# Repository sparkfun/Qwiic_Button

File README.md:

SparkFun Qwiic Button
========================================
<table class="table table-hover table-striped table-bordered">
  <tr align="center">
   <td></td>
   <td></td>
   <td></td>
  </tr>
  <tr align="center">
    <td><a href="https://www.sparkfun.com/products/15932">SparkFun Qwiic Button - Red <br />(BOB-15932)</a></td>
    <td><a href="https://www.sparkfun.com/products/16842">SparkFun Qwiic Button - Green <br />(BOB-16842)</a></td>
    <td><a href="https://www.sparkfun.com/products/15931">SparkFun Qwiic Button Breakout <br />(BOB-15931)</a></td>
  </tr>
</table>

The SparkFun Qwiic Button is an I<sup>2</sup>C enabled button with a built-in LED, interrupts, variable I<sup>2</sup>C address, and onboard button queues.

Repository Contents
-------------------

* **/Documentation** - Data sheets, additional product information
* **/Hardware** - Eagle design files (.brd, .sch)
* **/Firmware** - The latest firmware on the Qwiic Button boards
* **/Hardware/Production** - Production panel files (.brd)

Documentation
--------------
* **[SparkFun Qwiic Button Hookup Guide](https://learn.sparkfun.com/tutorials/sparkfun-qwiic-button-hookup-guide/all)** - Basic Hookup Guide.
* **[SparkFun Qwiic Button Arduino Library](https://github.com/sparkfun/SparkFun_Qwiic_Button_Arduino_Library)** - Arduino library for the Qwiic Button and Switch.
* **[SparkFun Qwiic Button Python Package](https://github.com/sparkfun/Qwiic_Button_Py)** - Python package for the Qwiic Button and Qwiic Switch

Product Versions
--------------

* [BOB-15932](https://www.sparkfun.com/products/15932) - SparkFun Red Version with red LED pushbutton
* [BOB-16842](https://www.sparkfun.com/products/16842) - SparkFun Red Version with green LED pushbutton
* [BOB-15931](https://www.sparkfun.com/products/15931) - SparkFun Red Version without button
* [SPX-15584](https://www.sparkfun.com/products/15584) - Original SparkX version of the Qwiic Button.

License Information
-------------------

This product is _**open source**_! 

Please review the LICENSE.md file for license information. 

If you have any questions or concerns on licensing, please contact technical support on our [SparkFun forums](https://forum.sparkfun.com/viewforum.php?f=152).

Distributed as-is; no warranty is given.

- Your friends at SparkFun.

_<COLLABORATION CREDIT>_

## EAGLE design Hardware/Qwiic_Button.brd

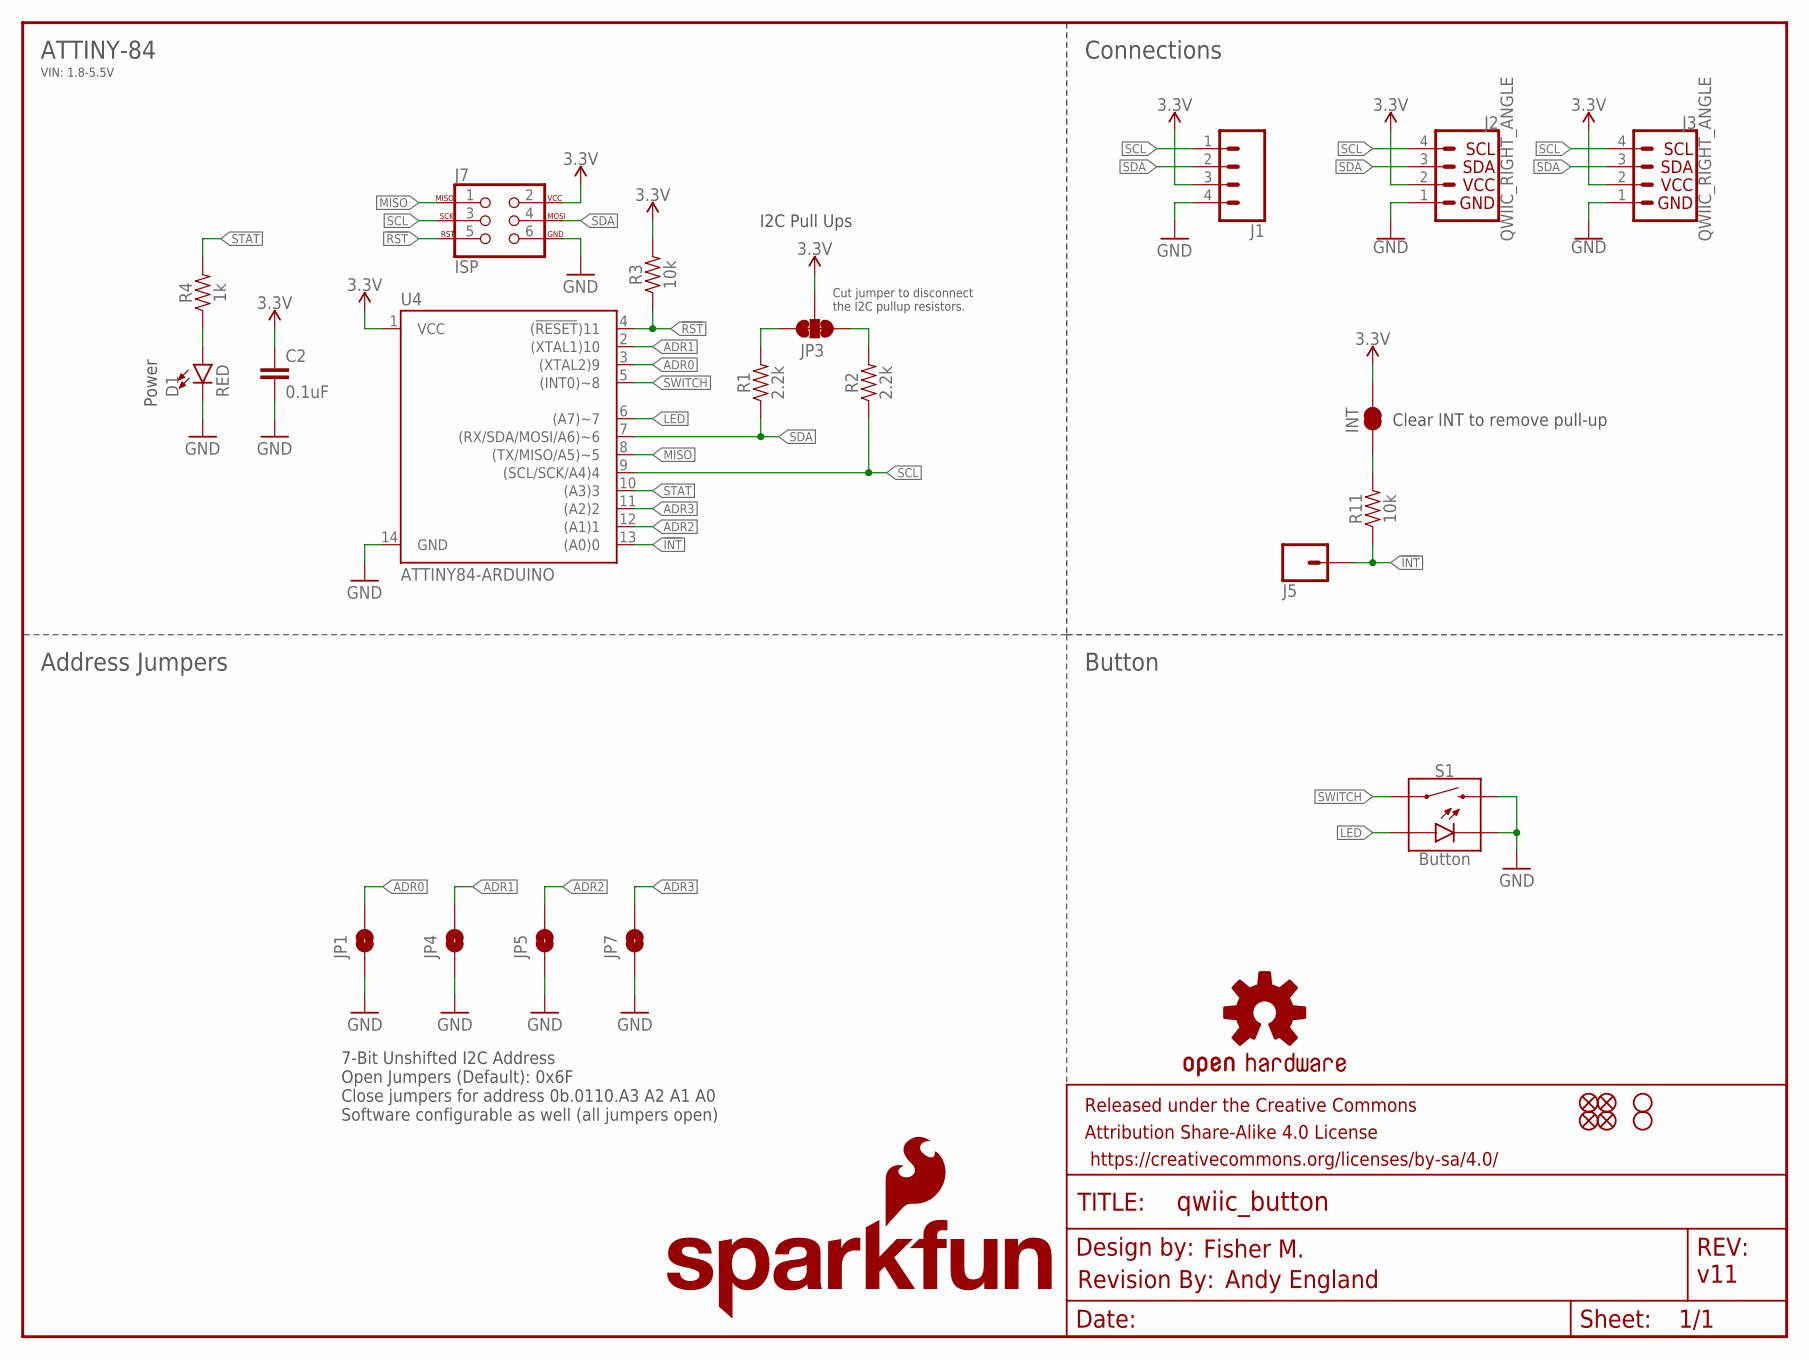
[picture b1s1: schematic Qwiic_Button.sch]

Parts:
C2: 0.1uF; 0603
D1: RED; LED-0603
FRAME1: FRAME-LETTER; CREATIVE_COMMONS
H1, H2: STAND-OFF
INT: JUMPER-SMT_2_NC_TRACE_SILK; SMT-JUMPER_2_NC_TRACE_SILK
J1: CONN_041X04_NO_SILK; 1X04_NO_SILK
J2, J3: QWIIC_RIGHT_ANGLE; JST04_1MM_RA
J5: CONN_01PTH_NO_SILK_YES_STOP; 1X01_NO_SILK
J7: ISP; 2X3_TEST_POINTS
JP1, JP4, JP5, JP7: JUMPER-SMT_2_NO_NO-SILK; SMT-JUMPER_2_NO_NO-SILK
JP2, JP6, JP8, JP9: FIDUCIALUFIDUCIAL; MICRO-FIDUCIAL
JP3: JUMPER-SMT_3_2-NC_TRACE_SILK; SMT-JUMPER_3_2-NC_TRACE_SILK
LOGO1: OSHW-LOGOMINI; OSHW-LOGO-MINI
LOGO2: REVISION
LOGO3: SFE_LOGO_NAME.1_INCH; SFE_LOGO_NAME_.1
LOGO4: SFE_LOGO_FLAME.1_INCH; SFE_LOGO_FLAME_.1
R1, R2: 2.2k; 0603
R3, R11: 10k; 0603
R4: 1k; 0603
S1: Button; TACTILE_SWITCH_LED_PTH_12MM
U4: ATTINY84-ARDUINO; SO14

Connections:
3.3V: C2.1, INT.2, J1.3, J2.2, J3.2, J7.2, JP3.2, R3.2, U4.1 (VCC)
!INT: J5.1, R11.1, U4.13 ((A0)0)
!RST: J7.5, R3.1, U4.4 ((!RESET!)11)
ADR0: JP1.2, U4.3 ((XTAL2)9)
ADR1: JP4.2, U4.2 ((XTAL1)10)
ADR2: JP5.2, U4.12 ((A1)1)
ADR3: JP7.2, U4.11 ((A2)2)
GND: C2.2, D1.C, J1.4, J2.1, J3.1, J7.6, JP1.1, JP4.1, JP5.1, JP7.1, S1.2, S1.C, U4.14 (GND)
INT_R: INT.1, R11.2
LED: S1.A, U4.6 ((A7)~7)
MISO: J7.1, U4.8 ((TX/MISO/A5)~5)
unnamed: D1.A, R4.1
SCL: J1.1, J2.4, J3.4, J7.3, R2.1, U4.9 ((SCL/SCK/A4)4)
SCL_PU1: JP3.1, R2.2
SDA: J1.2, J2.3, J3.3, J7.4, R1.1, U4.7 ((RX/SDA/MOSI/A6)~6)
SDA_PU1: JP3.3, R1.2
STAT: R4.2, U4.10 ((A3)3)
SWITCH: S1.4 (1), U4.5 ((INT0)~8)

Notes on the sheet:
v11
Connections
Cut jumper to disconnect the I2C pullup resistors.
7-Bit Unshifted I2C Address Open Jumpers (Default): 0x6F Close jumpers for address 0b.0110.A3 A2 A1 A0 Software configurable as well (all jumpers open)
I2C Pull Ups
Power
Clear INT to remove pull-up
Fisher M.
Andy England
ATTINY-84
Address Jumpers
Button
VIN: 1.8-5.5V

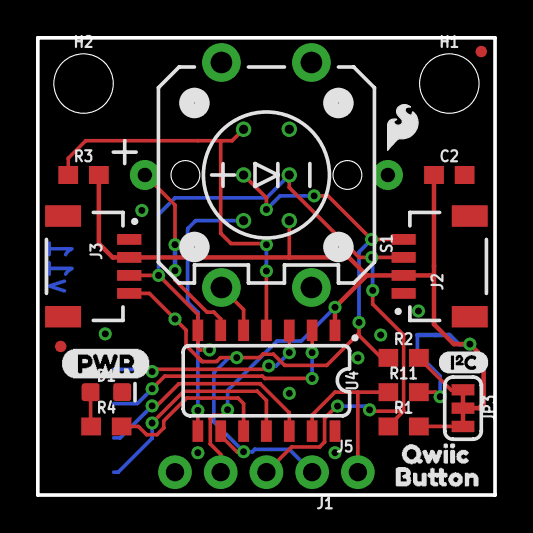
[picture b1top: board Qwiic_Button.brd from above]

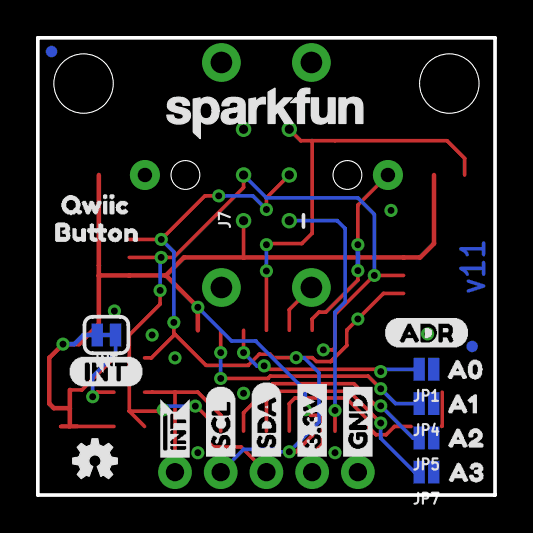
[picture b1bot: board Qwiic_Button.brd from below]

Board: 2 copper layers, 25.4 x 25.4 mm, 48 parts (23 on the bottom side), 18 nets.

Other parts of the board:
U$1, U$2: BUTTON1
U$3: PWR-()-04
U$4: INT-()-04
U$5: SCL
U$6: SDA
U$7: 3.3V
U$8: GND
U$9: (ADR)
U$10: I_SUPER2_C-()-03
U$15: INT#-[<-04
U$16: A00
U$17: A11
U$19: A22
U$20, U$23: QWIIC0
U$21: A33

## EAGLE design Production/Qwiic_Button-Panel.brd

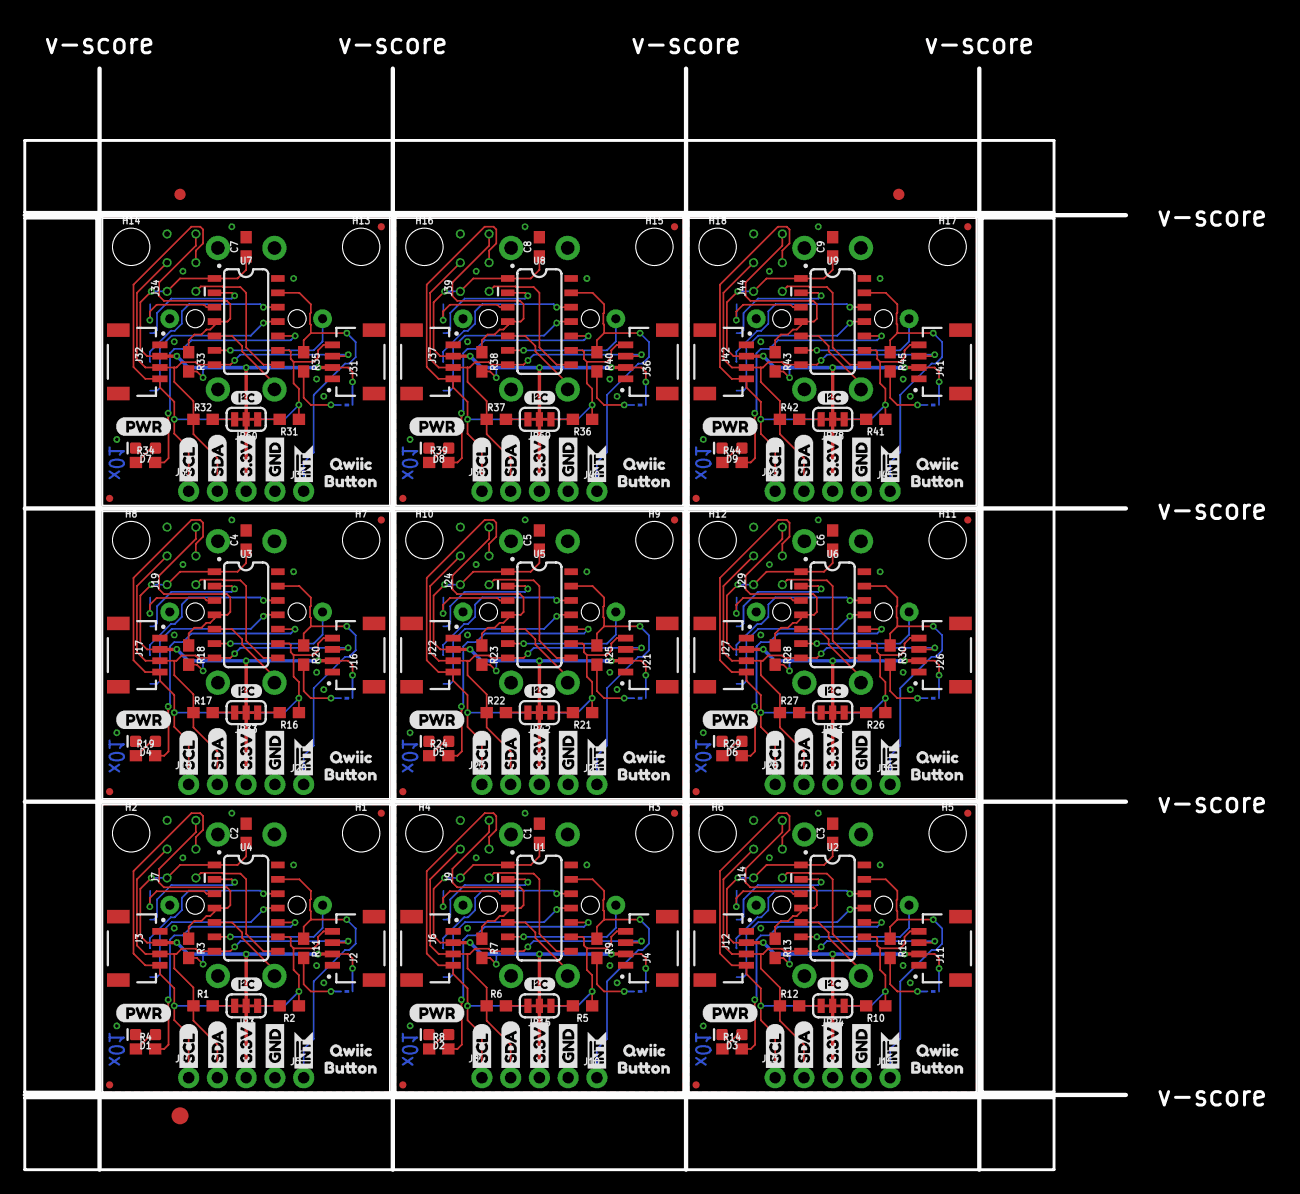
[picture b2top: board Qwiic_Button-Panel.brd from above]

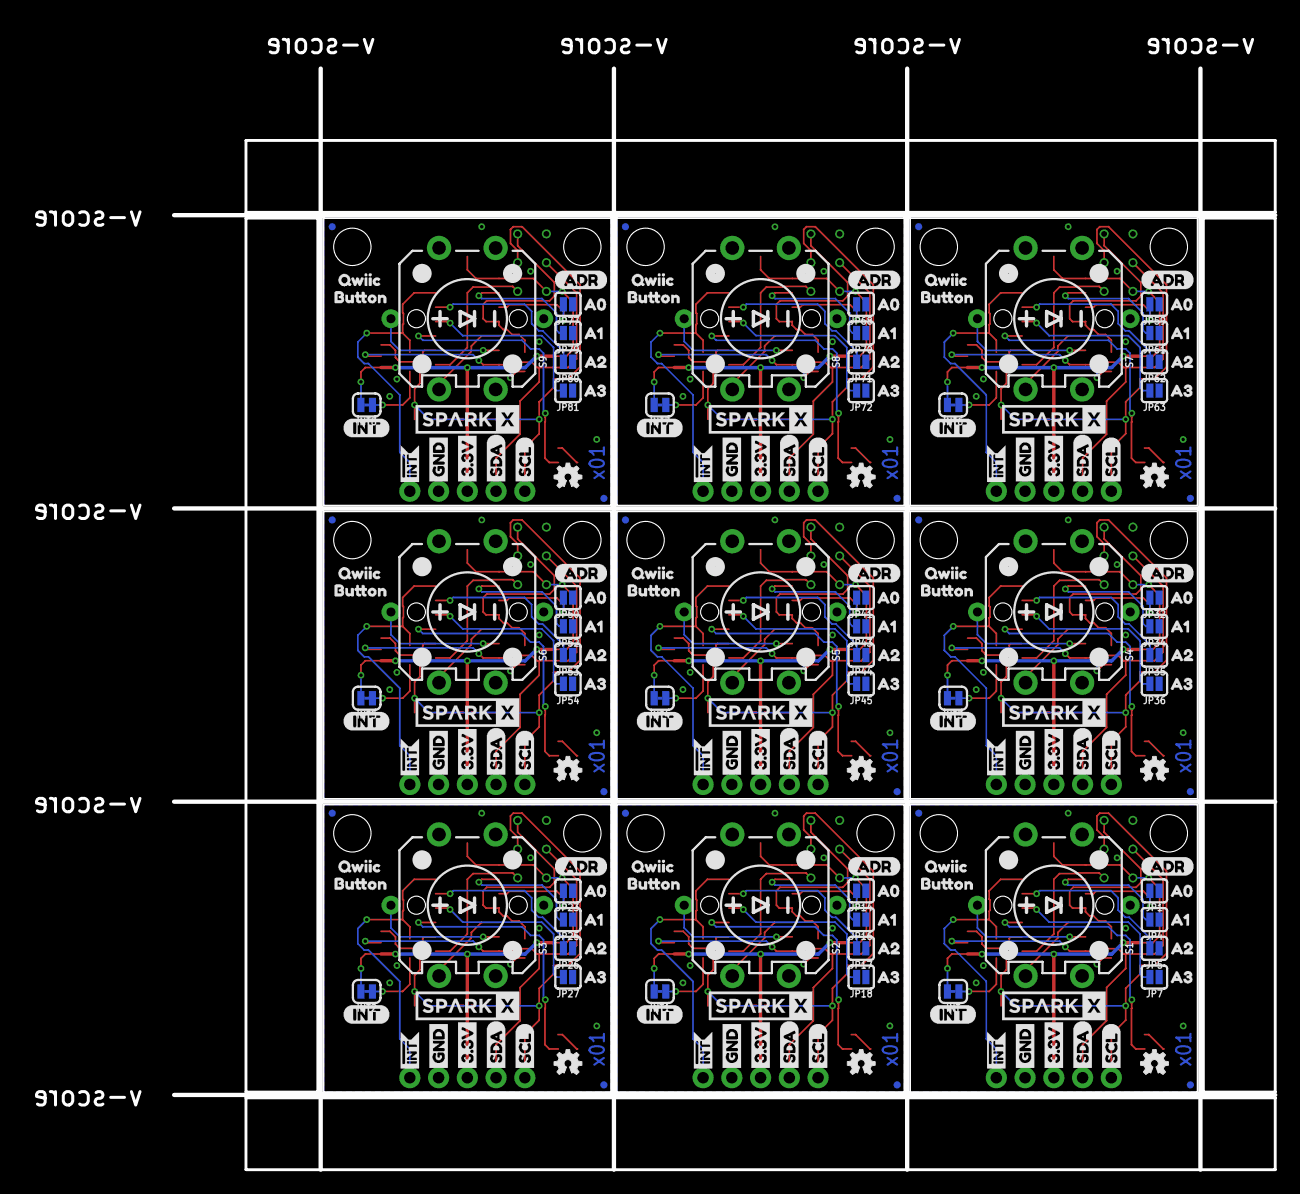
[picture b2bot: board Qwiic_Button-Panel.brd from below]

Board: 2 copper layers, 97.3 x 97.3 mm, 453 parts (207 on the bottom side), 162 nets.

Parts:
C1, C2, C3, C4, C5, C6, C7, C8, C9: 0.1uF; 0603
D1, D2, D3, D4, D5, D6, D7, D8, D9: RED; LED-0603
E$1, E$2: FIDUCIAL-1X2
E$3: FIDUCIAL-1.5X3
H1, H2, H3, H4, H5, H6, H7, H8, H9, H10, H11, H12, H13, H14, H15, H16, H17, H18: STAND-OFF
INT, INT1, INT2, INT3, INT4, INT5, INT6, INT7, INT8: SMT-JUMPER_2_NC_TRACE_SILK
J1, J8, J13, J18, J23, J28, J33, J38, J43: 1X04_NO_SILK
J2, J3, J4, J6, J11, J12, J16, J17, J21, J22, J26, J27, J31, J32, J36, J37, J41, J42: JST04_1MM_RA
J5, J10, J15, J20, J25, J30, J35, J40, J45: 1X01_NO_SILK
J7, J9, J14, J19, J24, J29, J34, J39, J44: ISP; 2X3_TEST_POINTS
JP1, JP4, JP5, JP7, JP14, JP16, JP17, JP18, JP23, JP25, JP26, JP27, JP32, JP34, JP35, JP36, JP41, JP43, JP44, JP45, JP50, JP52, JP53, JP54, JP59, JP61, JP62, JP63, JP68, JP70, JP71, JP72, JP77, JP79, JP80, JP81: SMT-JUMPER_2_NO_SILK
JP2, JP6, JP8, JP9, JP10, JP11, JP12, JP13, JP19, JP20, JP21, JP22, JP28, JP29, JP30, JP31, JP37, JP38, JP39, JP40, JP46, JP47, JP48, JP49, JP55, JP56, JP57, JP58, JP64, JP65, JP66, JP67, JP73, JP74, JP75, JP76: FIDUCIALUFIDUCIAL; MICRO-FIDUCIAL
JP3, JP15, JP24, JP33, JP42, JP51, JP60, JP69, JP78: SMT-JUMPER_3_2-NC_TRACE_SILK
LOGO1, LOGO2, LOGO3, LOGO4, LOGO5, LOGO6, LOGO7, LOGO8, LOGO9: OSHW-LOGOMINI; OSHW-LOGO-MINI
R1, R2, R5, R6, R10, R12, R16, R17, R21, R22, R26, R27, R31, R32, R36, R37, R41, R42: 2.2k; 0603
R3, R7, R9, R11, R13, R15, R18, R20, R23, R25, R28, R30, R33, R35, R38, R40, R43, R45: 10k; 0603
R4, R8, R14, R19, R24, R29, R34, R39, R44: 1k; 0603
S1, S2, S3, S4, S5, S6, S7, S8, S9: Button; TACTILE_SWITCH_LED_PTH_12MM
U1, U2, U3, U4, U5, U6, U7, U8, U9: ATTINY84-ARDUINO; SO14
U$1, U$2, U$38, U$39, U$61, U$62, U$84, U$85, U$107, U$108, U$130, U$131, U$153, U$154, U$176, U$177, U$199, U$200: BUTTON1
U$3, U$42, U$65, U$88, U$111, U$134, U$157, U$180, U$203: PWR-()-04
U$4, U$37, U$60, U$83, U$106, U$129, U$152, U$175, U$198: INT-()-04
U$5, U$14, U$24, U$34, U$47, U$57, U$70, U$80, U$93, U$103, U$116, U$126, U$139, U$149, U$162, U$172, U$185, U$195: SCL
U$6, U$12, U$25, U$33, U$48, U$56, U$71, U$79, U$94, U$102, U$117, U$125, U$140, U$148, U$163, U$171, U$186, U$194: SDA
U$7, U$22, U$26, U$30, U$49, U$53, U$72, U$76, U$95, U$99, U$118, U$122, U$141, U$145, U$164, U$168, U$187, U$191: 3.3V
U$8, U$13, U$27, U$29, U$50, U$52, U$73, U$75, U$96, U$98, U$119, U$121, U$142, U$144, U$165, U$167, U$188, U$190: GND
U$9, U$28, U$51, U$74, U$97, U$120, U$143, U$166, U$189: (ADR)
U$10, U$31, U$54, U$77, U$100, U$123, U$146, U$169, U$192: I_SUPER2_C-()-03
U$11, U$15, U$32, U$35, U$55, U$58, U$78, U$81, U$101, U$104, U$124, U$127, U$147, U$150, U$170, U$173, U$193, U$196: INT#-[<-04
U$16, U$43, U$66, U$89, U$112, U$135, U$158, U$181, U$204: A00
U$17, U$44, U$67, U$90, U$113, U$136, U$159, U$182, U$205: A11
U$18, U$36, U$59, U$82, U$105, U$128, U$151, U$174, U$197: SPARKX-MEDIUM
U$19, U$45, U$68, U$91, U$114, U$137, U$160, U$183, U$206: A22
U$20, U$23, U$40, U$41, U$63, U$64, U$86, U$87, U$109, U$110, U$132, U$133, U$155, U$156, U$178, U$179, U$201, U$202: QWIIC0
U$21, U$46, U$69, U$92, U$115, U$138, U$161, U$184, U$207: A33

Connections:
3.3V: C2.1, INT.2, J1.3, J2.2, J3.2, J7.2, JP3.2, R3.2, U4.1
3.3V1: C1.1, INT1.2, J4.2, J6.2, J8.3, J9.2, JP15.2, R7.2, U1.1
3.3V2: C3.1, INT2.2, J11.2, J12.2, J13.3, J14.2, JP24.2, R13.2, U2.1
3.3V3: C4.1, INT3.2, J16.2, J17.2, J18.3, J19.2, JP33.2, R18.2, U3.1
3.3V4: C5.1, INT4.2, J21.2, J22.2, J23.3, J24.2, JP42.2, R23.2, U5.1
3.3V5: C6.1, INT5.2, J26.2, J27.2, J28.3, J29.2, JP51.2, R28.2, U6.1
3.3V6: C7.1, INT6.2, J31.2, J32.2, J33.3, J34.2, JP60.2, R33.2, U7.1
3.3V7: C8.1, INT7.2, J36.2, J37.2, J38.3, J39.2, JP69.2, R38.2, U8.1
3.3V8: C9.1, INT8.2, J41.2, J42.2, J43.3, J44.2, JP78.2, R43.2, U9.1
!INT: J5.1, R11.1, U4.13
!INT1: J10.1, R9.1, U1.13
!INT2: J15.1, R15.1, U2.13
!INT3: J20.1, R20.1, U3.13
!INT4: J25.1, R25.1, U5.13
!INT5: J30.1, R30.1, U6.13
!INT6: J35.1, R35.1, U7.13
!INT7: J40.1, R40.1, U8.13
!INT8: J45.1, R45.1, U9.13
!RST: J7.5, R3.1, U4.4
!RST1: J9.5, R7.1, U1.4
!RST2: J14.5, R13.1, U2.4
!RST3: J19.5, R18.1, U3.4
!RST4: J24.5, R23.1, U5.4
!RST5: J29.5, R28.1, U6.4
!RST6: J34.5, R33.1, U7.4
!RST7: J39.5, R38.1, U8.4
!RST8: J44.5, R43.1, U9.4
ADR0: JP1.2, U4.3
ADR1: JP4.2, U4.2
ADR2: JP5.2, U4.12
ADR3: JP7.2, U4.11
ADR4: JP14.2, U1.3
ADR5: JP16.2, U1.2
ADR6: JP17.2, U1.12
ADR7: JP18.2, U1.11
ADR8: JP23.2, U2.3
ADR9: JP25.2, U2.2
ADR10: JP26.2, U2.12
ADR11: JP27.2, U2.11
ADR12: JP32.2, U3.3
ADR13: JP34.2, U3.2
ADR14: JP35.2, U3.12
ADR15: JP36.2, U3.11
ADR16: JP41.2, U5.3
ADR17: JP43.2, U5.2
ADR18: JP44.2, U5.12
ADR19: JP45.2, U5.11
ADR20: JP50.2, U6.3
ADR21: JP52.2, U6.2
ADR22: JP53.2, U6.12
ADR23: JP54.2, U6.11
ADR24: JP59.2, U7.3
ADR25: JP61.2, U7.2
ADR26: JP62.2, U7.12
ADR27: JP63.2, U7.11
ADR28: JP68.2, U8.3
ADR29: JP70.2, U8.2
ADR30: JP71.2, U8.12
ADR31: JP72.2, U8.11
ADR32: JP77.2, U9.3
ADR33: JP79.2, U9.2
ADR34: JP80.2, U9.12
ADR35: JP81.2, U9.11
GND: C2.2, D1.C, J1.4, J2.1, J3.1, J7.6, JP1.1, JP4.1, JP5.1, JP7.1, S1.2, S1.C, U4.14
GND1: C1.2, D2.C, J4.1, J6.1, J8.4, J9.6, JP14.1, JP16.1, JP17.1, JP18.1, S2.2, S2.C, U1.14
GND2: C3.2, D3.C, J11.1, J12.1, J13.4, J14.6, JP23.1, JP25.1, JP26.1, JP27.1, S3.2, S3.C, U2.14
GND3: C4.2, D4.C, J16.1, J17.1, J18.4, J19.6, JP32.1, JP34.1, JP35.1, JP36.1, S4.2, S4.C, U3.14
GND4: C5.2, D5.C, J21.1, J22.1, J23.4, J24.6, JP41.1, JP43.1, JP44.1, JP45.1, S5.2, S5.C, U5.14
GND5: C6.2, D6.C, J26.1, J27.1, J28.4, J29.6, JP50.1, JP52.1, JP53.1, JP54.1, S6.2, S6.C, U6.14
GND6: C7.2, D7.C, J31.1, J32.1, J33.4, J34.6, JP59.1, JP61.1, JP62.1, JP63.1, S7.2, S7.C, U7.14
GND7: C8.2, D8.C, J36.1, J37.1, J38.4, J39.6, JP68.1, JP70.1, JP71.1, JP72.1, S8.2, S8.C, U8.14
GND8: C9.2, D9.C, J41.1, J42.1, J43.4, J44.6, JP77.1, JP79.1, JP80.1, JP81.1, S9.2, S9.C, U9.14
INT_R: INT.1, R11.2
INT_R1: INT1.1, R9.2
INT_R2: INT2.1, R15.2
INT_R3: INT3.1, R20.2
INT_R4: INT4.1, R25.2
INT_R5: INT5.1, R30.2
INT_R6: INT6.1, R35.2
INT_R7: INT7.1, R40.2
INT_R8: INT8.1, R45.2
LED: S1.A, U4.6
LED1: S2.A, U1.6
LED2: S3.A, U2.6
LED3: S4.A, U3.6
LED4: S5.A, U5.6
LED5: S6.A, U6.6
LED6: S7.A, U7.6
LED7: S8.A, U8.6
LED8: S9.A, U9.6
MISO: J7.1, U4.8
MISO1: J9.1, U1.8
MISO2: J14.1, U2.8
MISO3: J19.1, U3.8
MISO4: J24.1, U5.8
MISO5: J29.1, U6.8
MISO6: J34.1, U7.8
MISO7: J39.1, U8.8
MISO8: J44.1, U9.8
unnamed: D2.A, R8.1
unnamed: D3.A, R14.1
unnamed: D1.A, R4.1
unnamed: D4.A, R19.1
unnamed: D5.A, R24.1
unnamed: D6.A, R29.1
unnamed: D7.A, R34.1
unnamed: D8.A, R39.1
unnamed: D9.A, R44.1
SCL: J1.1, J2.4, J3.4, J7.3, R2.1, U4.9
SCL1: J4.4, J6.4, J8.1, J9.3, R5.1, U1.9
SCL2: J11.4, J12.4, J13.1, J14.3, R10.1, U2.9
SCL3: J16.4, J17.4, J18.1, J19.3, R16.1, U3.9
SCL4: J21.4, J22.4, J23.1, J24.3, R21.1, U5.9
SCL5: J26.4, J27.4, J28.1, J29.3, R26.1, U6.9
SCL6: J31.4, J32.4, J33.1, J34.3, R31.1, U7.9
SCL7: J36.4, J37.4, J38.1, J39.3, R36.1, U8.9
SCL8: J41.4, J42.4, J43.1, J44.3, R41.1, U9.9
SCL_PU1: JP3.1, R2.2
SCL_PU2: JP15.1, R5.2
SCL_PU3: JP24.1, R10.2
SCL_PU4: JP33.1, R16.2
SCL_PU5: JP42.1, R21.2
SCL_PU6: JP51.1, R26.2
SCL_PU7: JP60.1, R31.2
SCL_PU8: JP69.1, R36.2
SCL_PU9: JP78.1, R41.2
SDA: J1.2, J2.3, J3.3, J7.4, R1.1, U4.7
SDA1: J4.3, J6.3, J8.2, J9.4, R6.1, U1.7
SDA2: J11.3, J12.3, J13.2, J14.4, R12.1, U2.7
SDA3: J16.3, J17.3, J18.2, J19.4, R17.1, U3.7
SDA4: J21.3, J22.3, J23.2, J24.4, R22.1, U5.7
SDA5: J26.3, J27.3, J28.2, J29.4, R27.1, U6.7
SDA6: J31.3, J32.3, J33.2, J34.4, R32.1, U7.7
SDA7: J36.3, J37.3, J38.2, J39.4, R37.1, U8.7
SDA8: J41.3, J42.3, J43.2, J44.4, R42.1, U9.7
SDA_PU1: JP3.3, R1.2
SDA_PU2: JP15.3, R6.2
SDA_PU3: JP24.3, R12.2
SDA_PU4: JP33.3, R17.2
SDA_PU5: JP42.3, R22.2
SDA_PU6: JP51.3, R27.2
SDA_PU7: JP60.3, R32.2
SDA_PU8: JP69.3, R37.2
SDA_PU9: JP78.3, R42.2
STAT: R4.2, U4.10
STAT1: R8.2, U1.10
STAT2: R14.2, U2.10
STAT3: R19.2, U3.10
STAT4: R24.2, U5.10
STAT5: R29.2, U6.10
STAT6: R34.2, U7.10
STAT7: R39.2, U8.10
STAT8: R44.2, U9.10
SWITCH: S1.4, U4.5
SWITCH1: S2.4, U1.5
SWITCH2: S3.4, U2.5
SWITCH3: S4.4, U3.5
SWITCH4: S5.4, U5.5
SWITCH5: S6.4, U6.5
SWITCH6: S7.4, U7.5
SWITCH7: S8.4, U8.5
SWITCH8: S9.4, U9.5

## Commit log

2019-11-27 changing silk, moving everything to one side for production
2019-12-02 post design review changes
2019-12-03 post checklist changes
2020-01-23 Create gitignore file.
    Added file.
2020-01-23 Create License.md file
    Added file.
2020-01-23 Create Issue Template File
    Added file.
2020-01-23 Created contributing file
    Added file.
2020-01-23 Updated ReadMe to add Hookup Guide
    Added Hookup Guide link.
2020-01-23 Update ReadMe
    Added links to SparkFun versions of Qwiic Button and Qwiic Button Breakout along with Hookup Guide. Updated photos for SparkFun version of Qwiic Buttons.
2020-01-23 cleaning repo for release, removing backup files
2020-01-23 adding polarity marker to button
2020-01-23 Update ReadMe
    Added Firmware to Repository Contents list.
2020-01-23 Update ReadMe
    Adding SparkX Product version for Qwiic Button (Red)
2020-01-23 Update ReadMe
    Removing old Firmware link from ReadMe. Firmware is now in the Repository Contents.
2021-02-24 Update README.md
    Add link for python package
2021-03-01 Update EEPROM_erase.ino
    Add loop() to sketch
2021-03-04 Update to Firmware - v01.03
    Changes made:
    Bump firmware version number
    Add disclaimer on PicChangeInterrupt lib
    Fixed comments on the listed bits on memory map
    Fixed bit order of queue status bit lists in protection map
    Updated pop() function to set full bool to false AFTER the tail has been incremented
2021-03-04 Remove excess hex files and generate new binary for the updated firmware

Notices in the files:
parts and their libraries:
SparkFun-Capacitors: Licensing: Creative Commons ShareAlike 4.0 International - https://creativecommons.org/licenses/by-sa/4.0
SparkFun-Aesthetics: Released under the Creative Commons Attribution Share-Alike 4.0 License
SparkFun-Aesthetics: https://creativecommons.org/licenses/by-sa/4.0
